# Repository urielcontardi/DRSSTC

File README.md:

# ARCSTRIKE

A **dual-resonant solid-state Tesla coil (DRSSTC)** project combining KiCad
electronics, resonator calculations, and a parametric enclosure with a unified
lid and resonator deck.

<p align="center"><em>Enclosure and resonator overview. The current CAD incorporates the unified lid and deck.</em></p>

<p align="center"><em>Assembled PCB — explore the interactive view in the project notebook.</em></p>

**Status:** assembly prototype. Physical fits, thermal behavior, and electrical
insulation still require validation. The primary wire holder remains pending.

## Quick start

| Task | File |
| --- | --- |
| Edit the electronics | [KiCad project](hardware/pcb/oneTesla.kicad_pro) |
| Print the enclosure | [STLs and quantities](mechanical/print/) |
| Assemble the enclosure | [Assembly guide](mechanical/README.md) · [Hardware BOM](mechanical/exports/hardware-BOM.csv) |
| Open the assembly in CAD | [STEP](mechanical/exports/ASSEMBLY.step) · [SolidCraft](mechanical/ASSEMBLY.sc) |
| Review the calculations | [Coil design](docs/design/COILS.md) |
| Explore the offline documentation | [Project notebook](docs/project/PROJECT-DRSSTC.html) |
| Inspect the PCB exports | [Gerbers, reports, and STEP](hardware/pcb/exports/) |

## Repository structure

```text
hardware/pcb/    KiCad project, local libraries, and PCB exports
mechanical/      Current enclosure sources, print files, assembly, and checks
docs/            Calculations, project notebook, and technical references
scripts/         PCB and documentation tools
```

The repository contains the current project. Earlier revisions are available
through Git history. Exported files stay alongside their sources in
`hardware/pcb/exports/` and `mechanical/exports/`. Printable STLs live in
`mechanical/print/`, with quantities included in their filenames.

## Reproduce the project

Run commands from the repository root:

```sh
# Recalculate the resonator (Python 3)
python3 -B scripts/calculate_resonator.py

# Rebuild the current enclosure (uv and CadQuery)
uv run --with cadquery python mechanical/build.py

# Validate all printable meshes
python3 -B mechanical/verify_stls.py

# Build the notebook and its offline ZIP (Python 3 and Node.js)
python3 -B scripts/build_project_document.py
```

Generated ZIPs and temporary results go to `output/`, which is ignored by Git.
Rebuilding CAD updates the exported files; review the reports and diff before
committing. The existing Gerbers represent the export documented in the
[PCB export notes](hardware/pcb/exports/README.md).

## Documentation

- [Electronics and KiCad libraries](hardware/pcb/README.md)
- [Enclosure assembly and printing](mechanical/README.md)
- [Technical documentation index](docs/README.md)
- [Tools and validation commands](scripts/README.md)
- [Maintenance conventions](CONTRIBUTING.md)

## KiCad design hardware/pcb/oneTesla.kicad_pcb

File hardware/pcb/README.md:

# PCB — active project

Open [oneTesla.kicad_pro](oneTesla.kicad_pro) in KiCad.

| Path | Purpose |
| --- | --- |
| `oneTesla.kicad_sch` | Electrical schematic |
| `oneTesla.kicad_pcb` | PCB layout |
| `oneTesla.kicad_dru` | Custom design rules |
| `library/oneTesla.kicad_sym` | Local symbols |
| `library/*.pretty/` | Local footprint libraries |
| `library/3dmodels/` | 3D models and source notices |
| `fp-lib-table`, `sym-lib-table` | Local library references |

Library paths use `${KIPRJMOD}/library/...`; keep the libraries alongside the project.
See [PCB exports](exports/) and [tools](../../scripts/README.md).

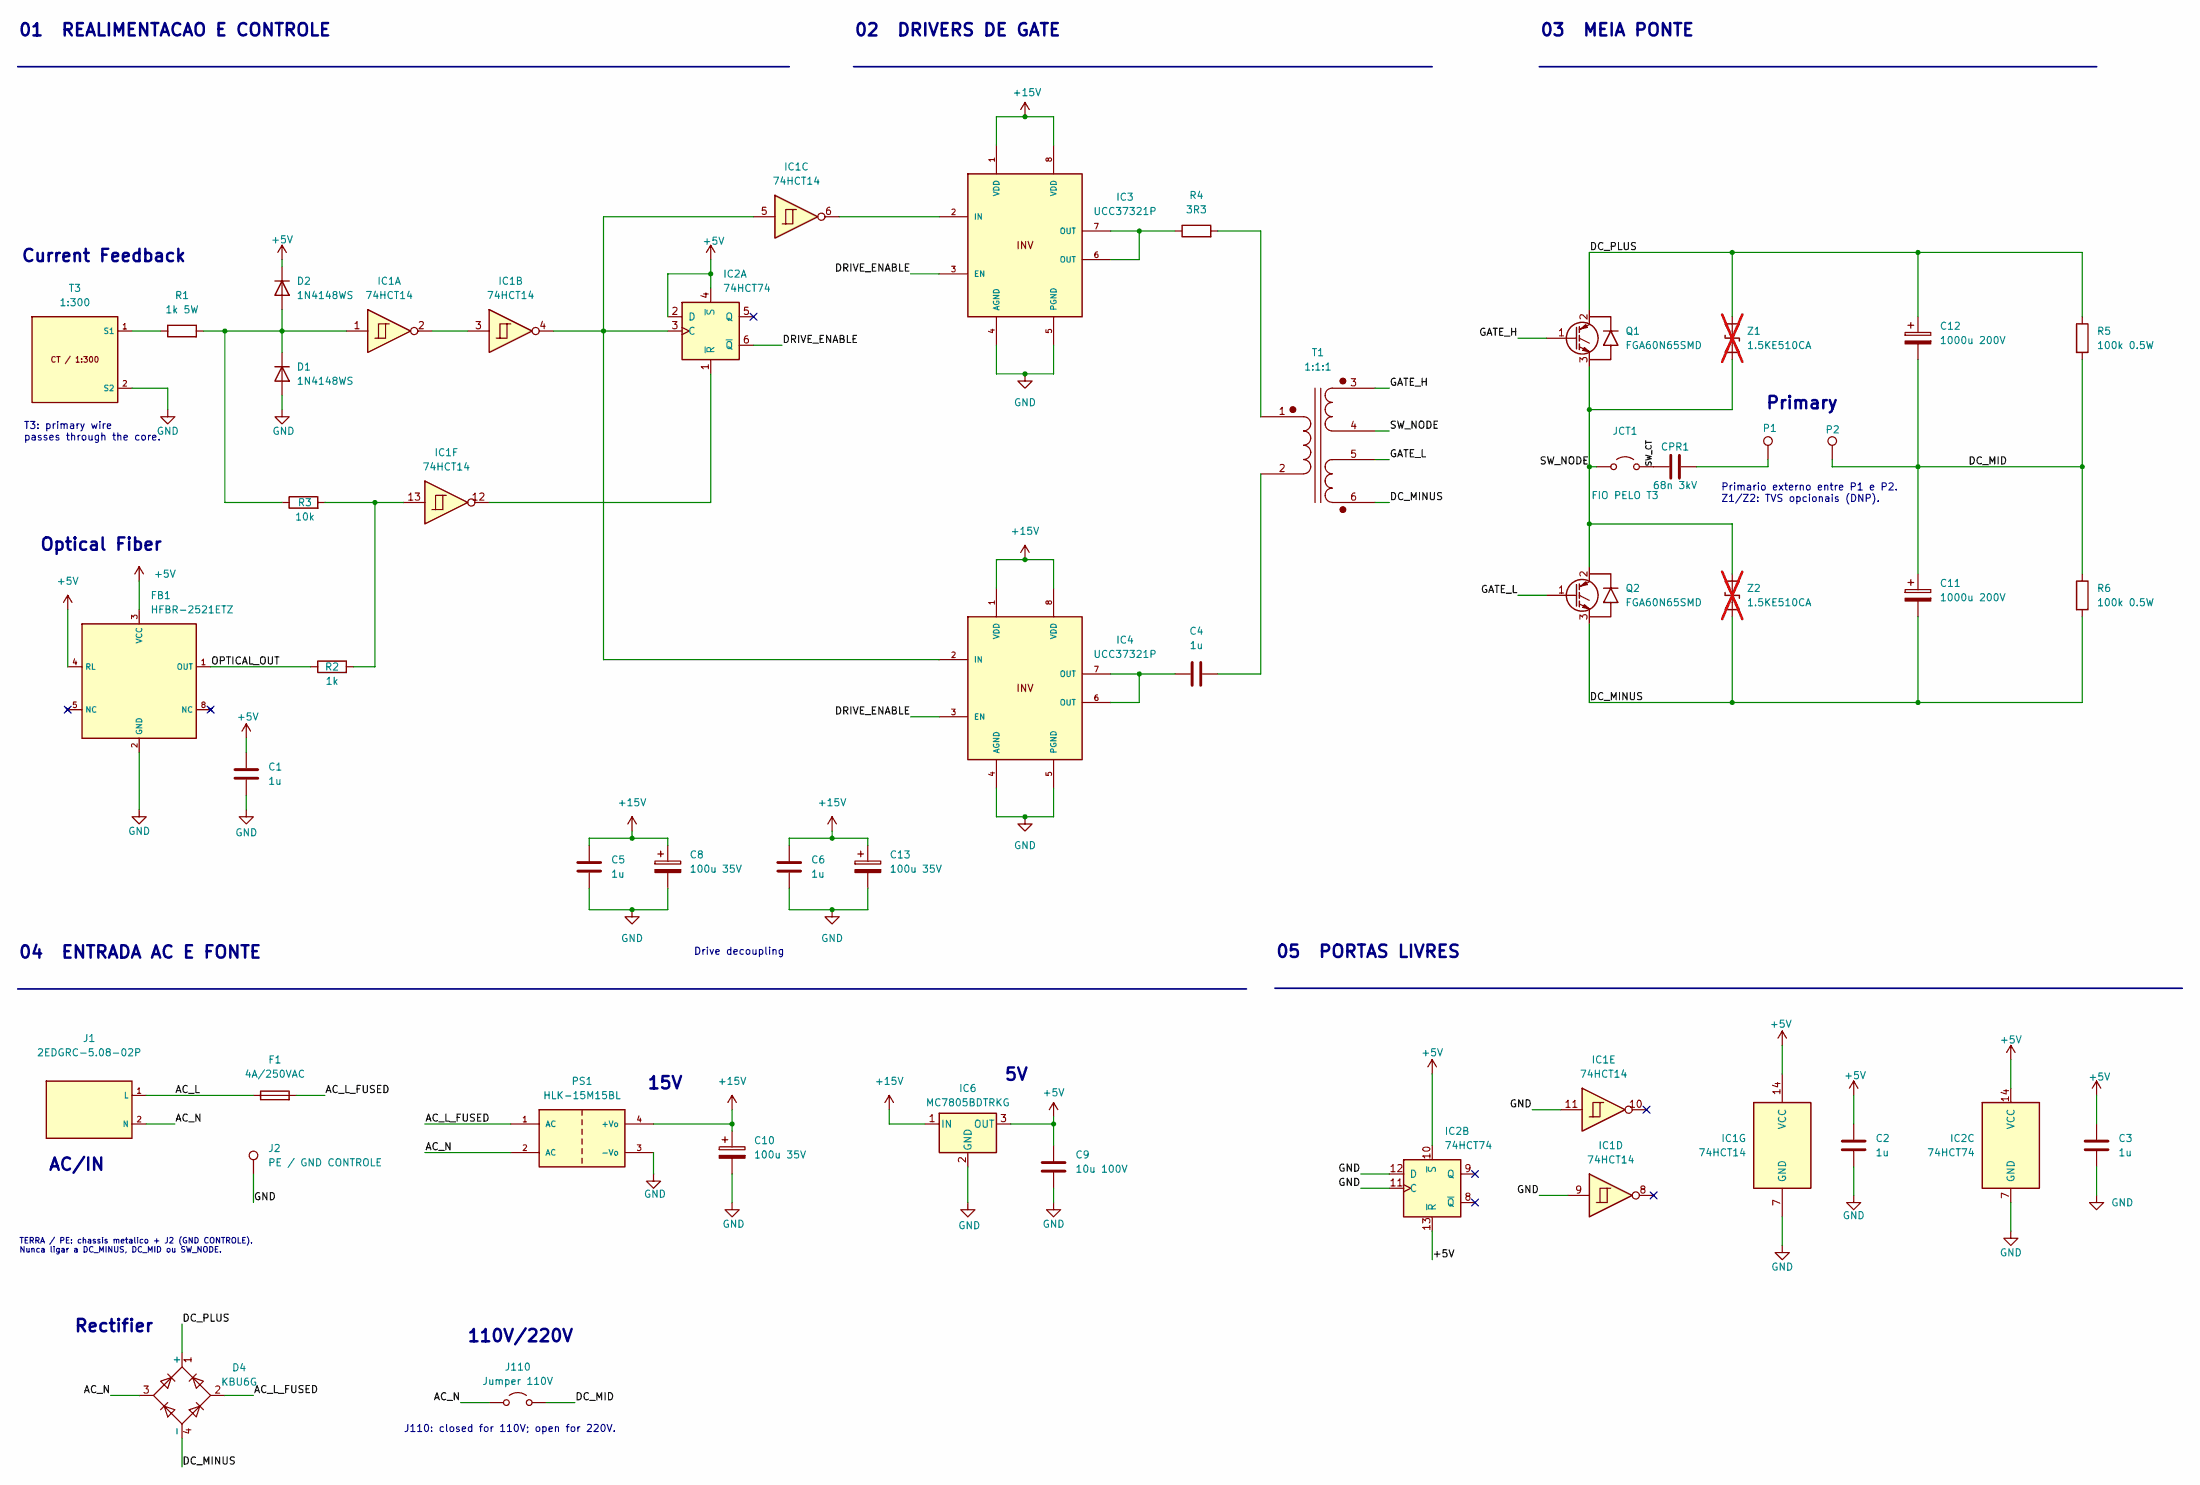
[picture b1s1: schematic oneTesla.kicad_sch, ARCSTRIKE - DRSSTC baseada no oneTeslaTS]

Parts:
C1, C3, C5, C6: 1u; C_0805_2012Metric_Pad1.18x1.45mm_HandSolder
C2: 1u; C_0805_2012Metric_Pad1.18x1.45mm_HandSolder_DFM_C2
C4: 1u; C_Disc_D7.5mm_W2.5mm_P5.00mm
C8: 100u 35V; CP_Elec_8x10_DFM_C8
C9: 10u 100V; C_1210_3225Metric
C10: 100u 35V; CP_Elec_8x10
C11: 1000u 200V; CP_SnapIn_D30.3_H40.5_P10.00_ReviewPending
C12: 1000u 200V; CP_SnapIn_D30.3_H40.5_P10.00_ReviewPending_DFM_C12
C13: 100u 35V; CP_Elec_8x10_DFM_C13
CPR1: 68n 3kV; CDE_940C30S68K_F_UNVERIFIED_DFM_CPR1
D1, D2: 1N4148WS; D_SOD-323_HandSoldering
D4: KBU6G; Diode_Bridge_Vishay_KBU_DFM_D4
F1: 4A/250VAC; Fuseholder_Idall_AS-06_5x20mm_Slotted_P22.35mm
FB1: HFBR-2521ETZ; HFBR-2521ETZ_DFM_FB1
IC1: 74HCT14; SOIC-14_3.9x8.7mm_P1.27mm
IC2: 74HCT74; SOIC-14_3.9x8.7mm_P1.27mm
IC3: UCC37321P; DIP-8_W7.62mm_Socket_LongPads_DFM_IC3
IC4: UCC37321P; DIP-8_W7.62mm_Socket_LongPads_DFM_IC4
IC6: MC7805BDTRKG; TO-252-3_TabPin2
J1: 2EDGRC-5.08-02P; TerminalBlock_2EDGRC-5.08_1x02_P5.08mm_Horizontal_DFM_J1
J2: PE / GND CONTROLE; PE_GND_Control_M3_D7.0mm_DFM_J2
J110: Jumper 110V; J110_WireLink_P15.24mm_DFM_J110
JCT1: FIO PELO T3; CT_Primary_WireLink_P21.59mm
P1: PRIMARIO A; Primary_WirePad_D4.0mm_Drill2.2mm
P2: PRIMARIO B; Primary_WirePad_D4.0mm_Drill2.2mm
PS1: HLK-15M15BL; HLK-15M15BL_DFM_PS1
Q1: FGA60N65SMD; Q_TO3P_ImportedPads_ReviewPending_DFM_Q1
Q2: FGA60N65SMD; Q_TO3P_ImportedPads_ReviewPending_DFM_Q2
R1: 1k 5W; R_Axial_Vishay_AC05_L18.0mm_D7.5mm_P10.16mm_Vertical_DFM_R1
R2: 1k; R_1206_3216Metric
R3: 10k; R_1206_3216Metric
R4: 3R3; R_Axial_DIN0207_L6.3mm_D2.5mm_P7.62mm_Horizontal
R5, R6: 100k 0.5W; R_Uniroyal_HV12_2512_P6.60mm
T1: 1:1:1; GDT_6Pin_UNVERIFIED
T3: 1:300; CT_1_300_P12.70mm_UNVERIFIED
Z1: 1.5KE510CA; D_DO201AD_P14.732_ReviewPending_DFM_Z1; not fitted
Z2: 1.5KE510CA; D_DO201AD_P14.732_ReviewPending_DFM_Z2; not fitted

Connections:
+5V: C1.1, C2.1, C3.1, C9.1, D2.1 (K), FB1.3 (VCC), FB1.4 (RL), IC1.14 (VCC), IC2.2 (D), IC2.4 (~S), IC2.10 (~S), IC2.13 (~R), IC2.14 (VCC), IC6.3 (OUT)
+15V: C5.1, C6.1, C8.1, C10.1, C13.1, IC3.1 (VDD), IC3.8 (VDD), IC4.1 (VDD), IC4.8 (VDD), IC6.1 (IN), PS1.4 (+Vo)
/AC_L: F1.1, J1.1 (L)
/AC_L_FUSED: D4.2, F1.2, PS1.1 (AC)
/AC_N: D4.3, J1.2 (N), J110.1 (A), PS1.2 (AC)
/DC_MID: C11.1, C12.2, J110.2 (B), P2.1 (1_1), R5.2, R6.1
/DC_MINUS: C11.2, D4.4 (-), Q2.3 (E), R6.2, T1.6 (SD), Z2.2 (A2)
/DC_PLUS: C12.1, D4.1 (+), Q1.2 (C), R5.1, Z1.1 (A1)
/DRIVE_ENABLE: IC2.6 (~Q), IC3.3 (EN), IC4.3 (EN)
/GATE_H: Q1.1 (G), T1.3 (SA)
/GATE_L: Q2.1 (G), T1.5 (SC)
/OPTICAL_OUT: FB1.1 (OUT), R2.1
/SW_CT: CPR1.1, JCT1.2 (B)
/SW_NODE: JCT1.1 (A), Q1.3 (E), Q2.2 (C), T1.4 (SB), Z1.2 (A2), Z2.1 (A1)
GND: C1.2, C2.2, C3.2, C5.2, C6.2, C8.2, C9.2, C10.2, C13.2, D1.2 (A), FB1.2 (GND), IC1.7 (GND), IC1.9, IC1.11, IC2.7 (GND), IC2.11 (C), IC2.12 (D), IC3.4 (AGND), IC3.5 (PGND), IC4.4 (AGND), IC4.5 (PGND), IC6.2 (GND), J2.1, PS1.3 (-Vo), T3.2 (S2)
unnamed: C4.1, IC4.6 (OUT), IC4.7 (OUT)
unnamed: CPR1.2, P1.1 (1_1)
unnamed: D1.1 (K), D2.2 (A), IC1.1, R1.2, R3.1
unnamed: IC1.2, IC1.3
unnamed: IC1.13, R2.2, R3.2
unnamed: IC1.4, IC1.5, IC2.3 (C), IC4.2 (IN)
unnamed: IC1.12, IC2.1 (~R)
unnamed: IC1.6, IC3.2 (IN)
unnamed: IC3.6 (OUT), IC3.7 (OUT), R4.1
unnamed: R4.2, T1.1 (AA)
unnamed: C4.2, T1.2 (AB)
unnamed: R1.1, T3.1 (S1)

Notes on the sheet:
110V/220V
01 REALIMENTACAO E CONTROLE
03 MEIA PONTE
T3: primary wire passes through the core.
J110: closed for 110V; open for 220V.
04 ENTRADA AC E FONTE
Drive decoupling
Current Feedback
AC/IN
Rectifier
Primario externo entre P1 e P2. Z1/Z2: TVS opcionais (DNP).
15V
02 DRIVERS DE GATE
05 PORTAS LIVRES
Optical Fiber
Primary
TERRA / PE: chassis metalico + J2 (GND CONTROLE). Nunca ligar a DC_MINUS, DC_MID ou SW_NODE.

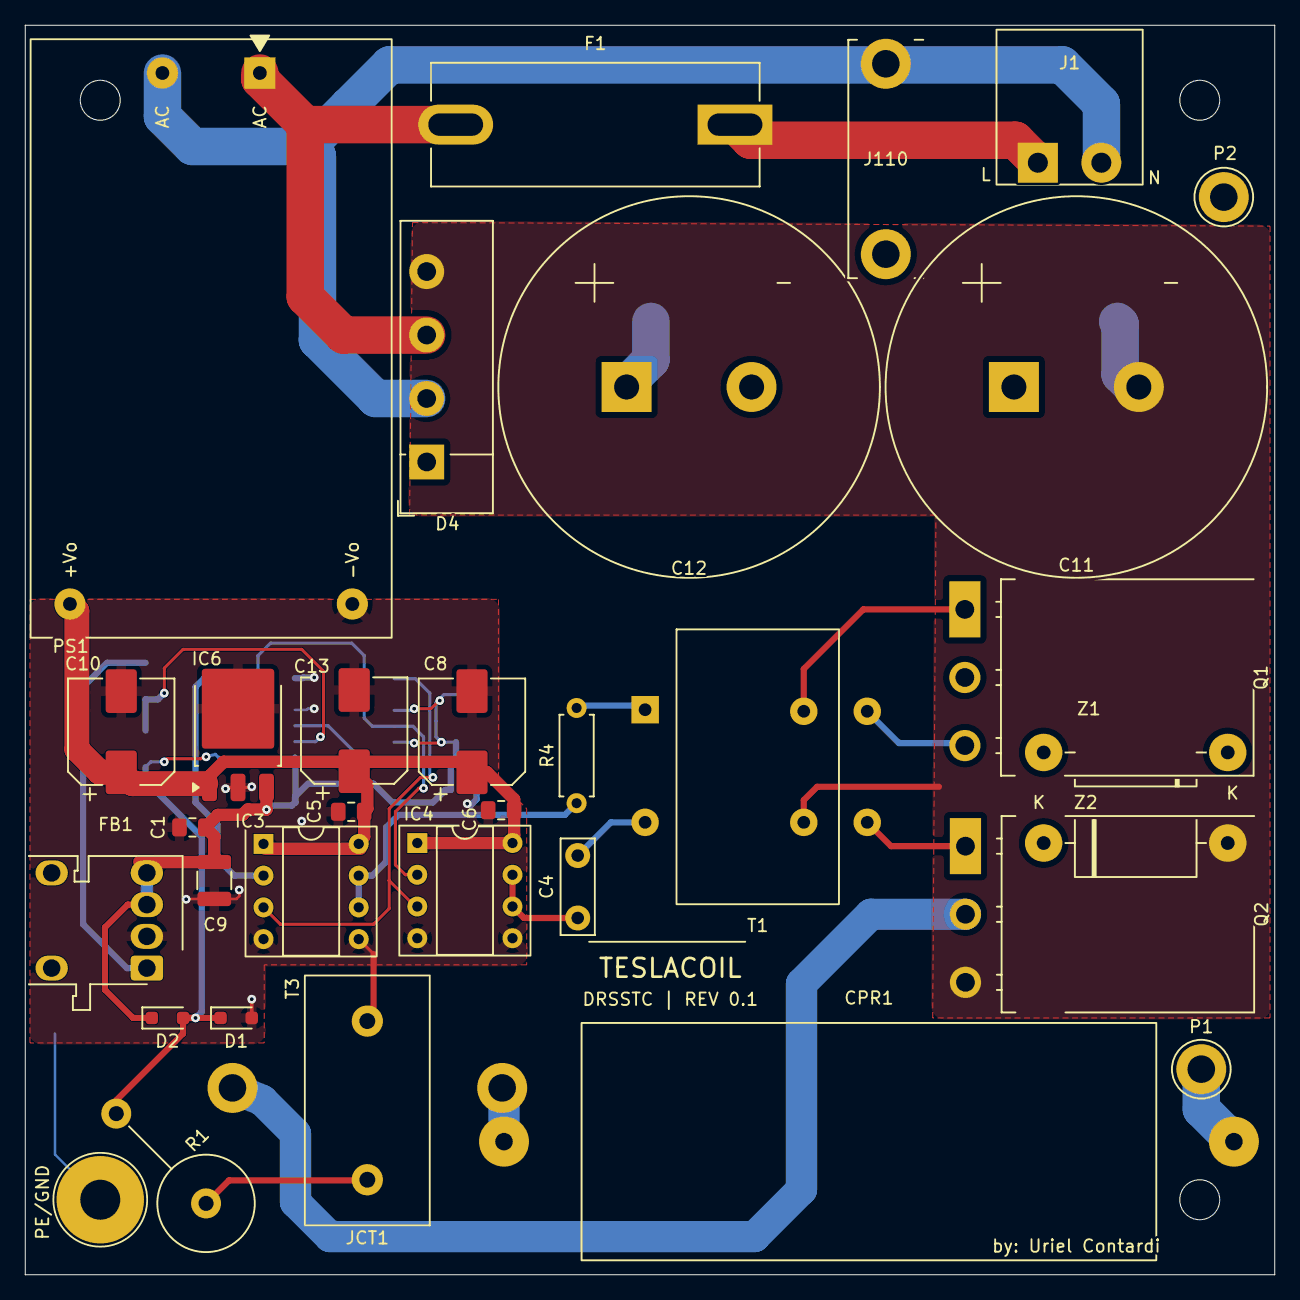
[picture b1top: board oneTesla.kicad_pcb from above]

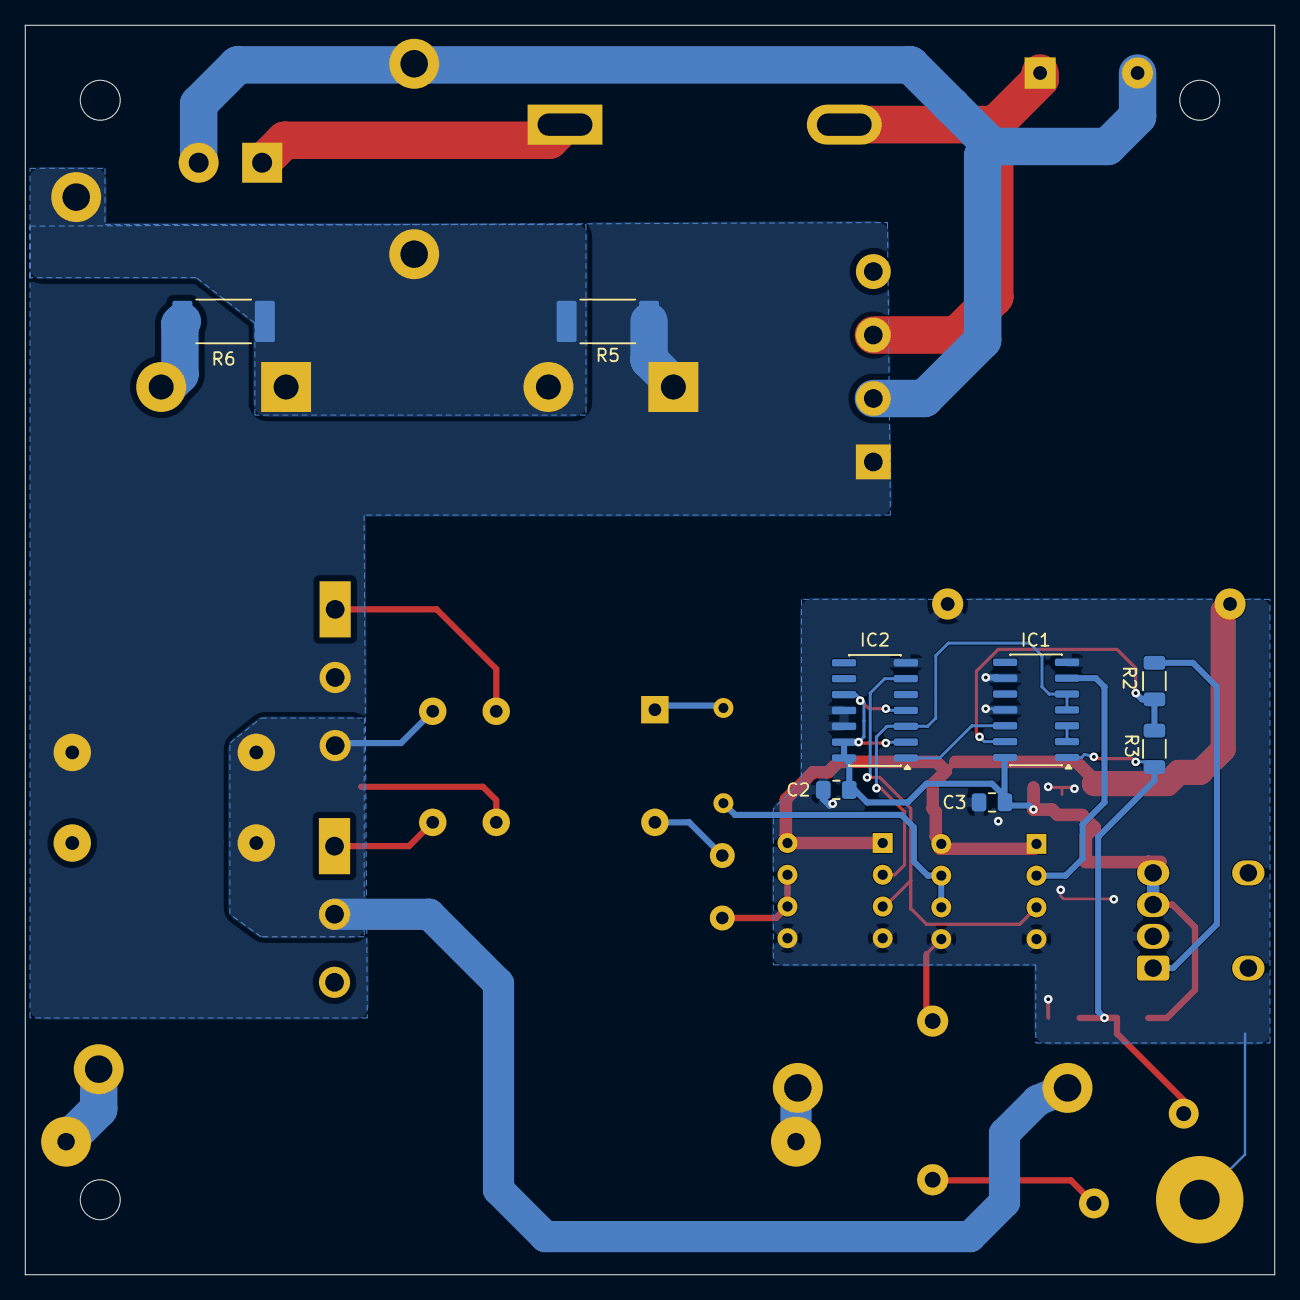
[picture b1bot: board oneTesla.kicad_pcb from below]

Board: 2 copper layers, 100.0 x 100.0 mm, 42 parts (8 on the bottom side), 27 nets.

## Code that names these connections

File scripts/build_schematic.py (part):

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fb=put('HFBR-2521ETZ','FB1','HFBR-2521ETZ',27.94,102.87)
power(fb,3,'+5V');power(fb,4,'+5V');power(fb,2,'GND');nc(fb,5);nc(fb,8)
r2=put('R','R2','1k',62.23,100.33,90)
wire(at(fb,1),at(r2,1));label('OPTICAL_OUT',(40.64,100.33))
r3=put('R','R3','10k',62.23,85.09,90);net(r3,1,'CT_SIGNAL')
u=put('74HCT14','IC1','74HCT14',104.14,100.33,unit=6)
wire(at(r2,2),(78.74,100.33),at(u,13));wire(at(r3,2),(78.74,85.09),(78.74,100.33));junction((78.74,100.33));label('RESET_MIX',(78.74,85.09));nc(u,12)
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wire((223.52,73.66),at(r4,1));wire((223.52,134.62),at(c4,1))
t1=put('GDT','T1','1:1:1',274.32,101.6,note='Pontos em 1/3/6 indicam a fase eletrica exigida (gates opostos); validar bobinas, numeros fisicos e fase da peca.')
wire(at(r4,2),(251.46,73.66),(251.46,96.52),at(t1,1));wire(at(c4,2),(251.46,134.62),(251.46,106.68),at(t1,2))
for pin,n in [(3,'GATE_H'),(4,'SW_NODE'),(5,'GATE_L'),(6,'DC_MINUS')]:net(t1,pin,n)
# Local decoupling banks for IC3 and IC4, shared short rails.
for ceramic,electrolytic,y in [('C5','C8',45.72),('C6','C7',162.56)]:
 ca=put('C',ceramic,'1u',241.3,y)
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q1=put('FGA60N65SMD','Q1','FGA60N65SMD',322.58,55.88,refpos=(334.01,46.99),valpos=(334.01,49.53),field_justify='left')
q2=put('FGA60N65SMD','Q2','FGA60N65SMD',322.58,101.6,refpos=(334.01,92.71),valpos=(334.01,95.25),field_justify='left')
net(q1,1,'GATE_H');net(q2,1,'GATE_L')
wire(at(q1,3),(325.12,78.74),at(q2,2));junction((325.12,78.74));label('SW_NODE',(325.12,78.74))
z1=put('1.5KE510CA','Z1','1.5KE510CA',350.52,55.88,270,dnp=True,refpos=(346.71,53.34),valpos=(346.71,55.88),field_justify='right',note='Opcional / DNP, como informado no manual, etapa 6. Nao incluido no kit.')
z2=put('1.5KE510CA','Z2','1.5KE510CA',350.52,101.6,270,dnp=True,refpos=(346.71,99.06),valpos=(346.71,101.6),field_justify='right',note='Opcional / DNP, como informado no manual, etapa 6. Nao incluido no kit.')
c12=put('C_Polarized','C12','1000u 200V',363.22,55.88,fp=CP1000)
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r6=put('R','R6','100k 0.5W',394.97,101.6,fp=RFH,refpos=(394.97,92.71),valpos=(394.97,95.25))
wire(at(q1,2),(325.12,40.64),(350.52,40.64),(363.22,40.64),(394.97,40.64))
for u in [z1,c12,r5]:wire(at(u,1),(at(u,1)[0],40.64))
junction((350.52,40.64));junction((363.22,40.64));label('DC_PLUS',(325.12,40.64))
wire(at(c12,2),(363.22,78.74),at(c11,1));wire(at(r5,2),(394.97,78.74),at(r6,1));wire((363.22,78.74),(394.97,78.74))
junction((363.22,78.74));junction((394.97,78.74));label('DC_MID',(374.65,78.74))
wire(at(q2,3),(325.12,120.65),(350.52,120.65),(363.22,120.65),(394.97,120.65))
for u in [z2,c11,r6]:wire(at(u,2),(at(u,2)[0],120.65))
junction((350.52,120.65));junction((363.22,120.65));label('DC_MINUS',(325.12,120.65))
wire(at(z1,2),(350.52,71.12),(325.12,71.12));junction((325.12,71.12))
wire(at(z2,1),(350.52,86.36),(325.12,86.36));junction((325.12,86.36))
cpr=put('ResonantCap','CPR1','68n 3kV',340.36,78.74,90,refpos=(340.36,65.405),valpos=(340.36,67.945),note='CDE 940C30S68K-F, 0.068uF/3000V, conforme layout. Confirmar mecanica.')
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# AC entry and isolated supply.
jac=put('IEC_C6','J1','IEC C6',25.4,209.55)
f1=put('Fuse','F1','4A/250VAC',58.42,204.47,90,note='Lista do kit: 4A. Serigrafia antiga menciona 10A; nao assumir 10A como valor do kit.')
wire(at(jac,1),at(f1,1));label('AC_L',(40.64,204.47));net(f1,2,'AC_L_FUSED')
net(jac,2,'AC_N');net(jac,3,'PE')
pe=put('Terminal','J2','PE/CHASSIS',58.42,222.25,fp='oneTesla:Chassis_PE_M3',note='Ponto explicito de ligacao PE ao chassis; inferido da trilha de terra e fixacao do layout.');net(pe,1,'PE')
d4=put('KBU6G','D4','KBU6G',111.76,208.28,90,refpos=(142.24,198.12),valpos=(142.24,200.66),note='Familia KBU selecionada pela ponte linear do layout; confirmar codigo da peca.')
for pin,n in [(1,'DC_PLUS'),(2,'AC_L_FUSED'),(3,'AC_N'),(4,'DC_MINUS')]:net(d4,pin,n)
j110=put('Jumper','J110','Jumper 110V',177.8,204.47,note='Liga AC_N ao ponto medio dos capacitores para dobrador em 110V. Manter aberto para 220V.')
net(j110,1,'AC_N');net(j110,2,'DC_MID')
text_('J110: fechado em 110V; aberto em 220V.',124.46,222.25,1.27)
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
